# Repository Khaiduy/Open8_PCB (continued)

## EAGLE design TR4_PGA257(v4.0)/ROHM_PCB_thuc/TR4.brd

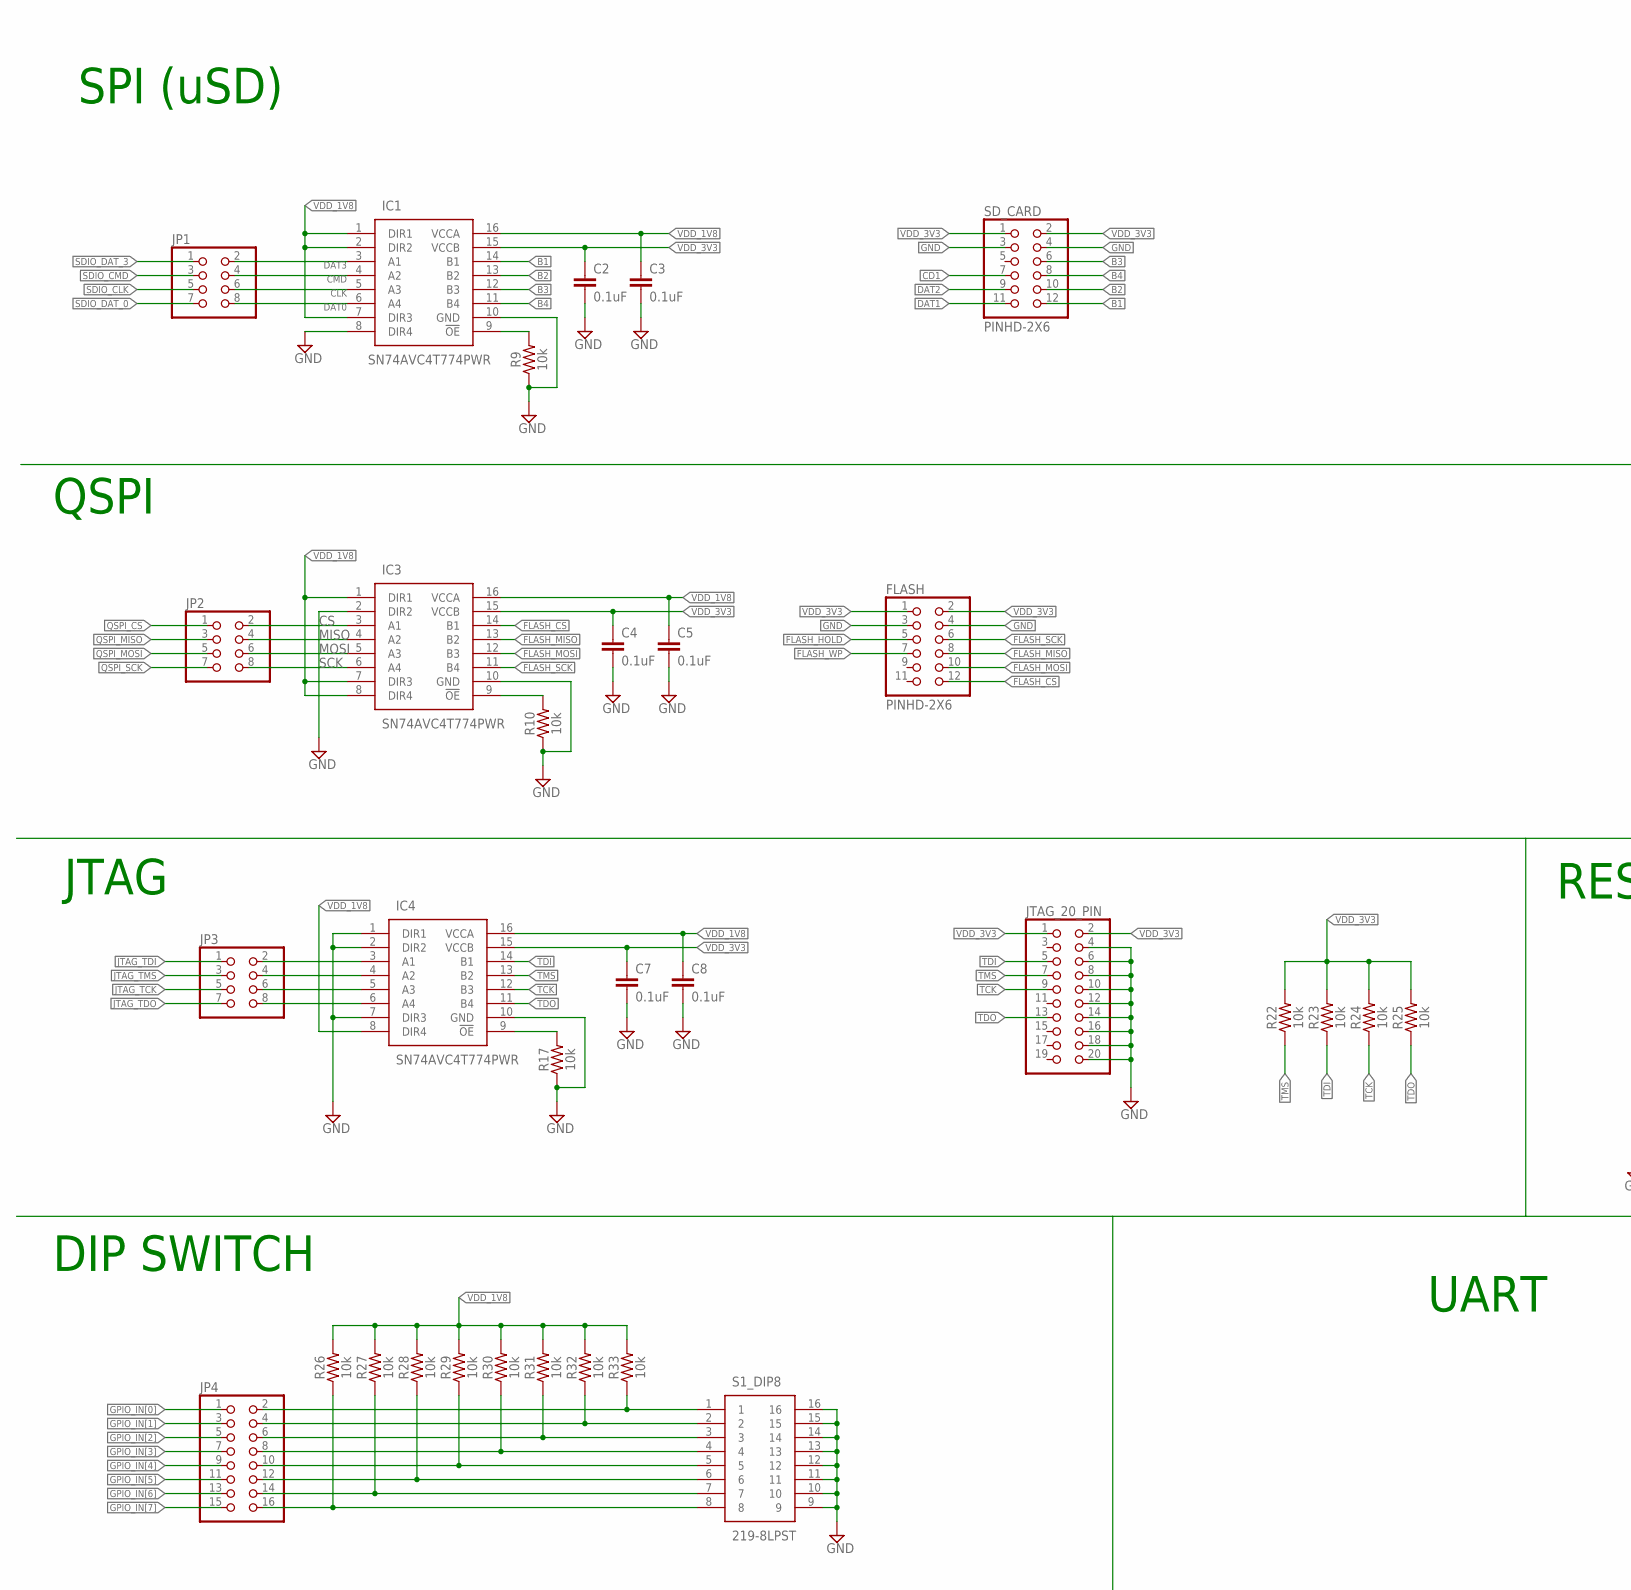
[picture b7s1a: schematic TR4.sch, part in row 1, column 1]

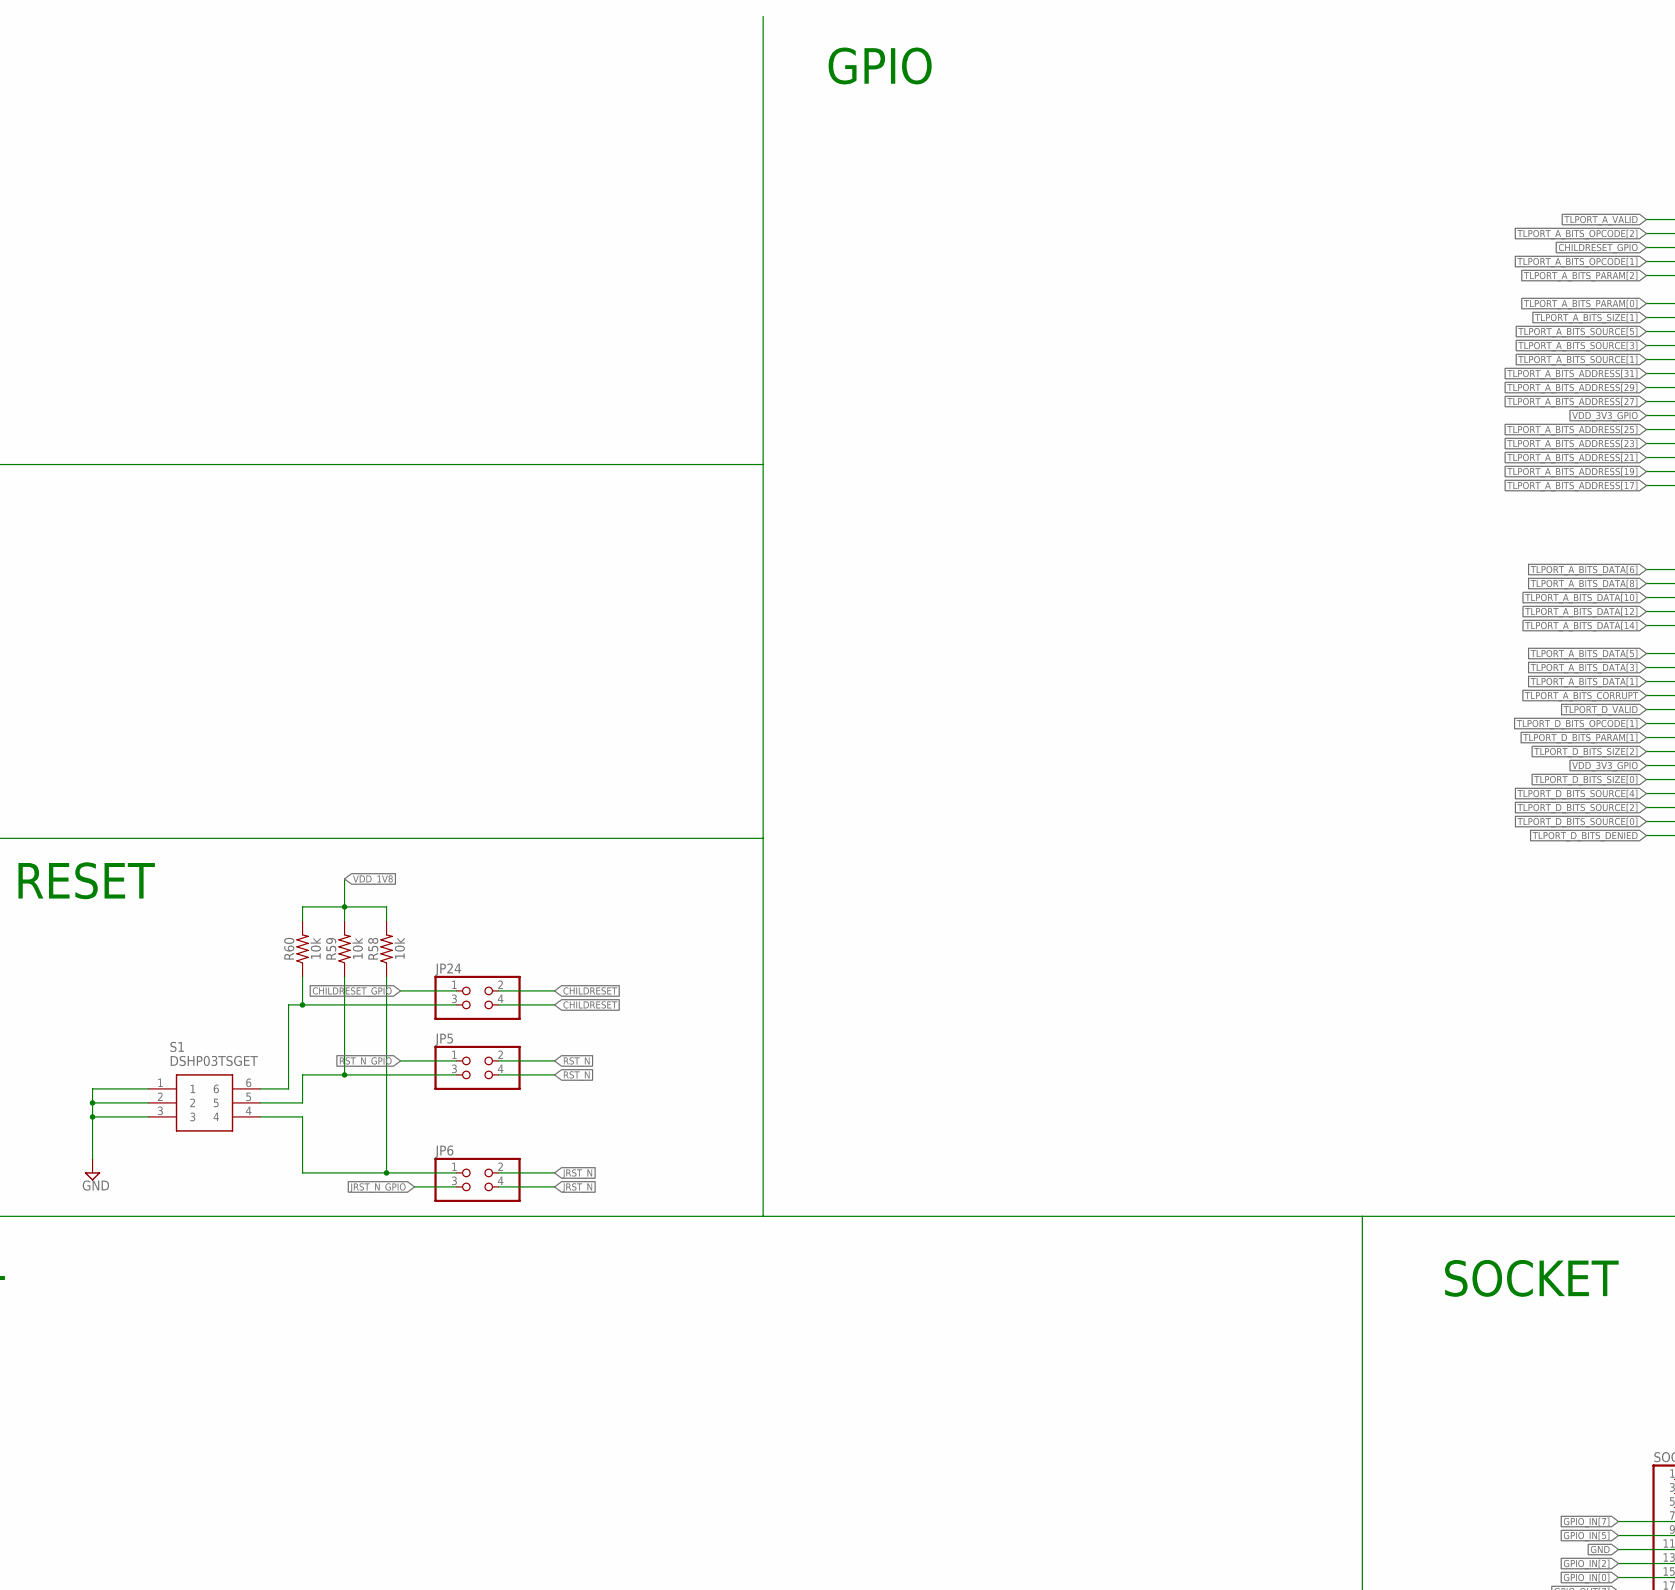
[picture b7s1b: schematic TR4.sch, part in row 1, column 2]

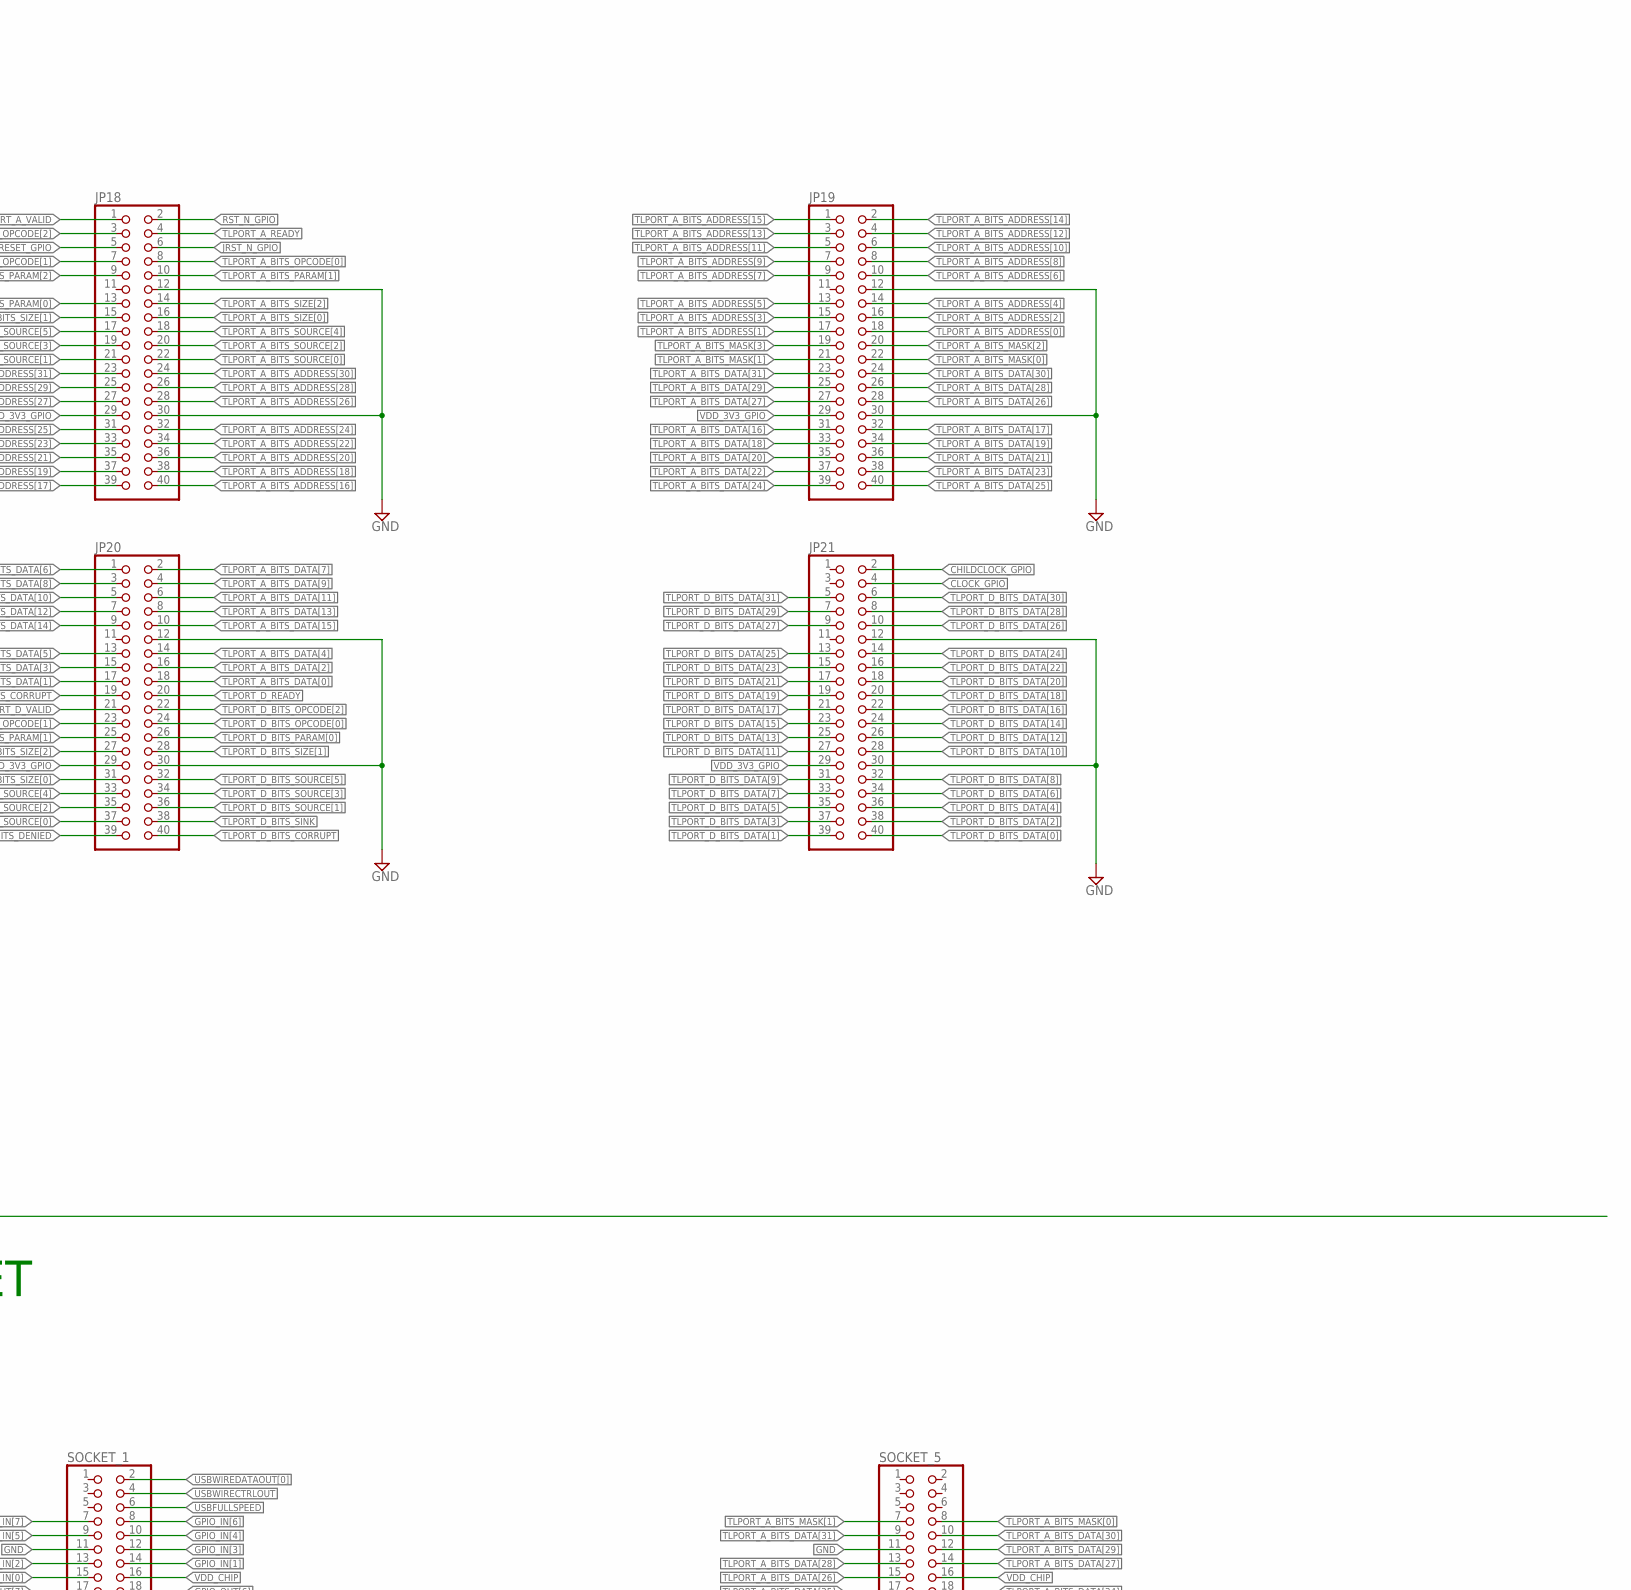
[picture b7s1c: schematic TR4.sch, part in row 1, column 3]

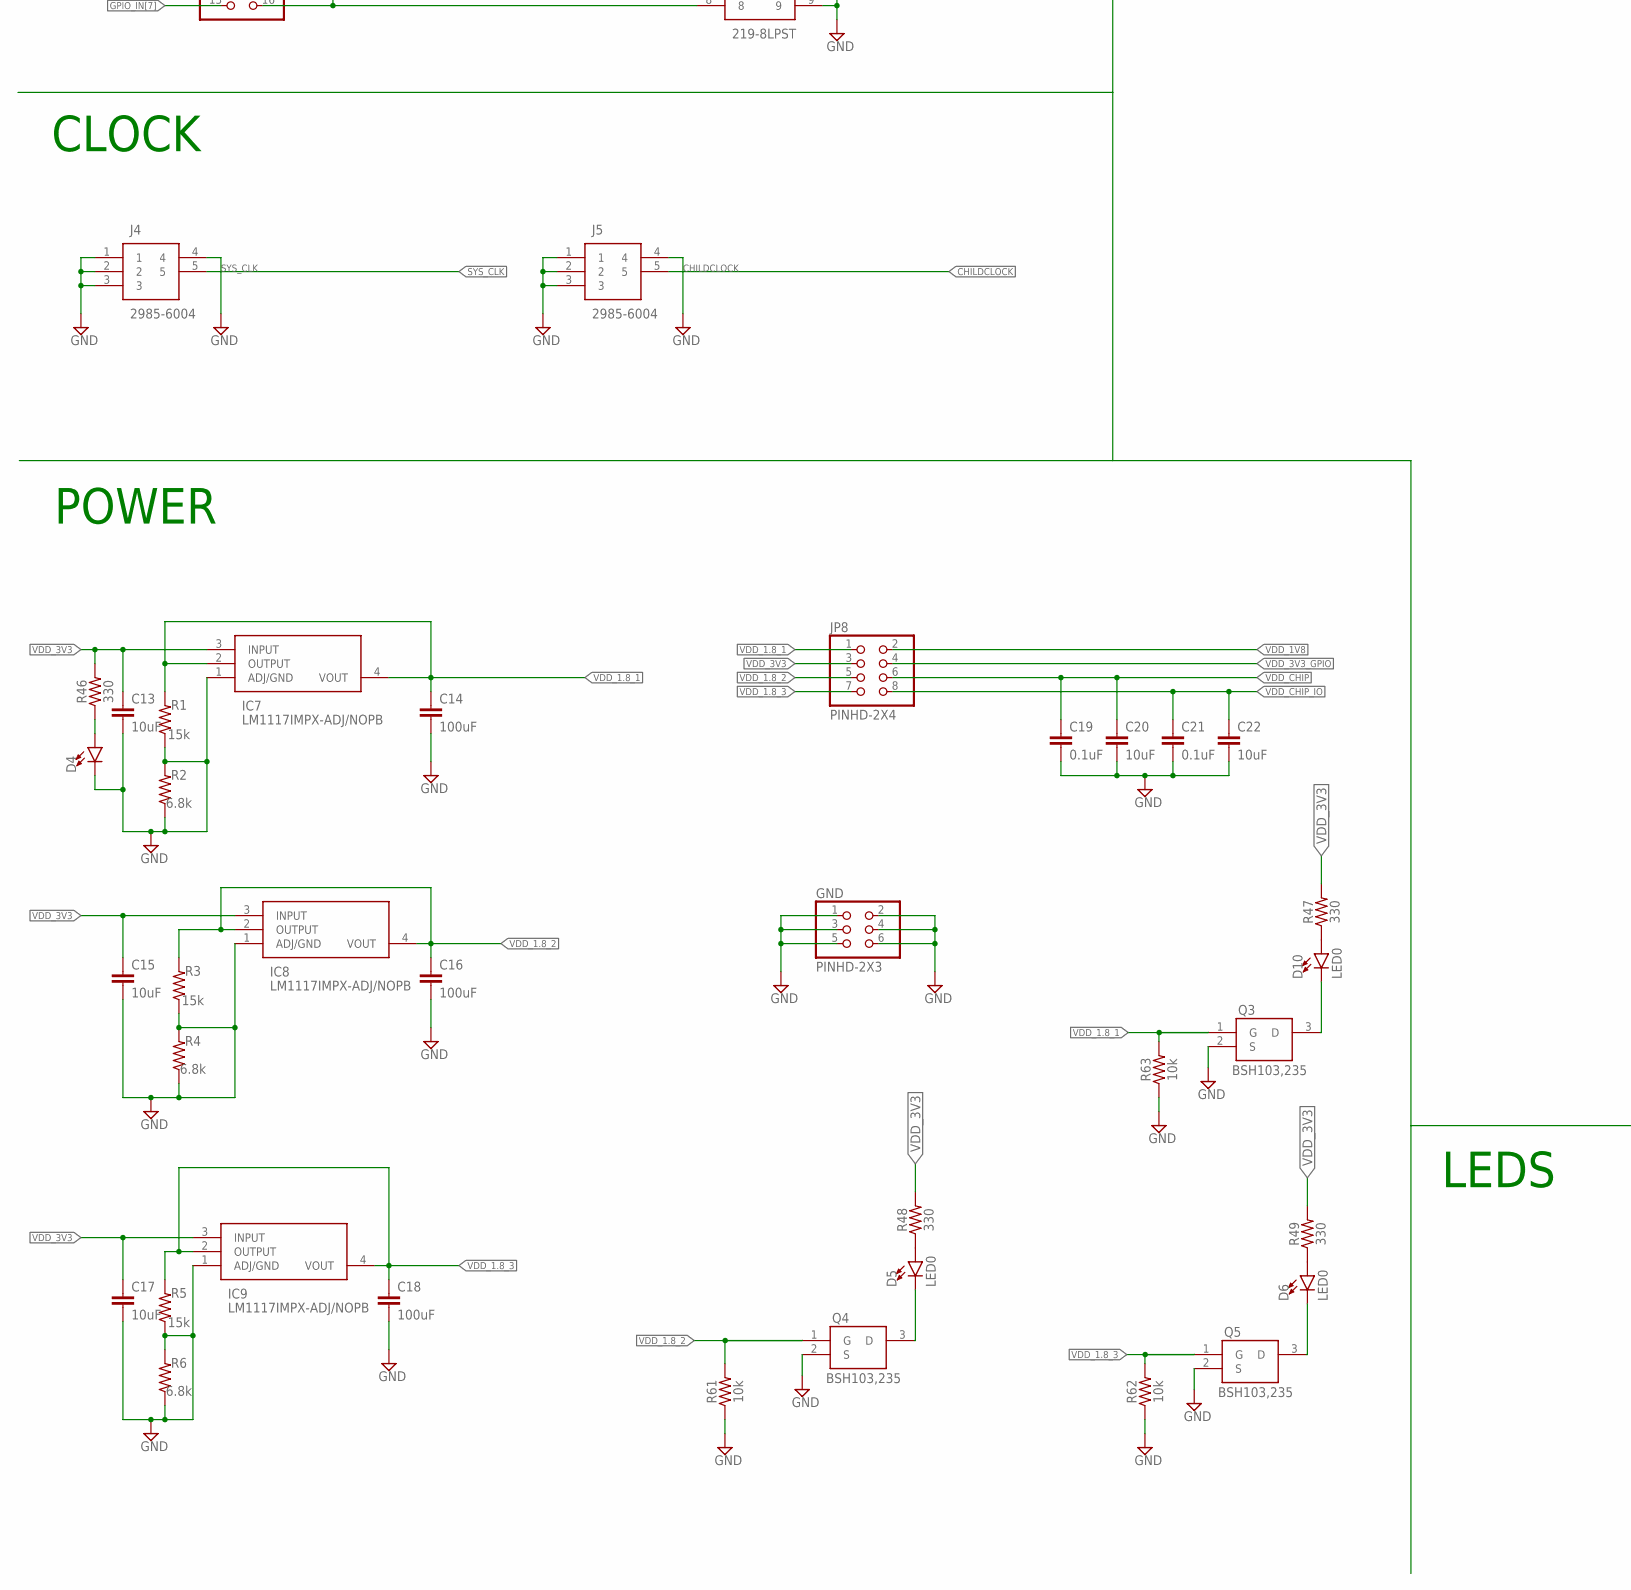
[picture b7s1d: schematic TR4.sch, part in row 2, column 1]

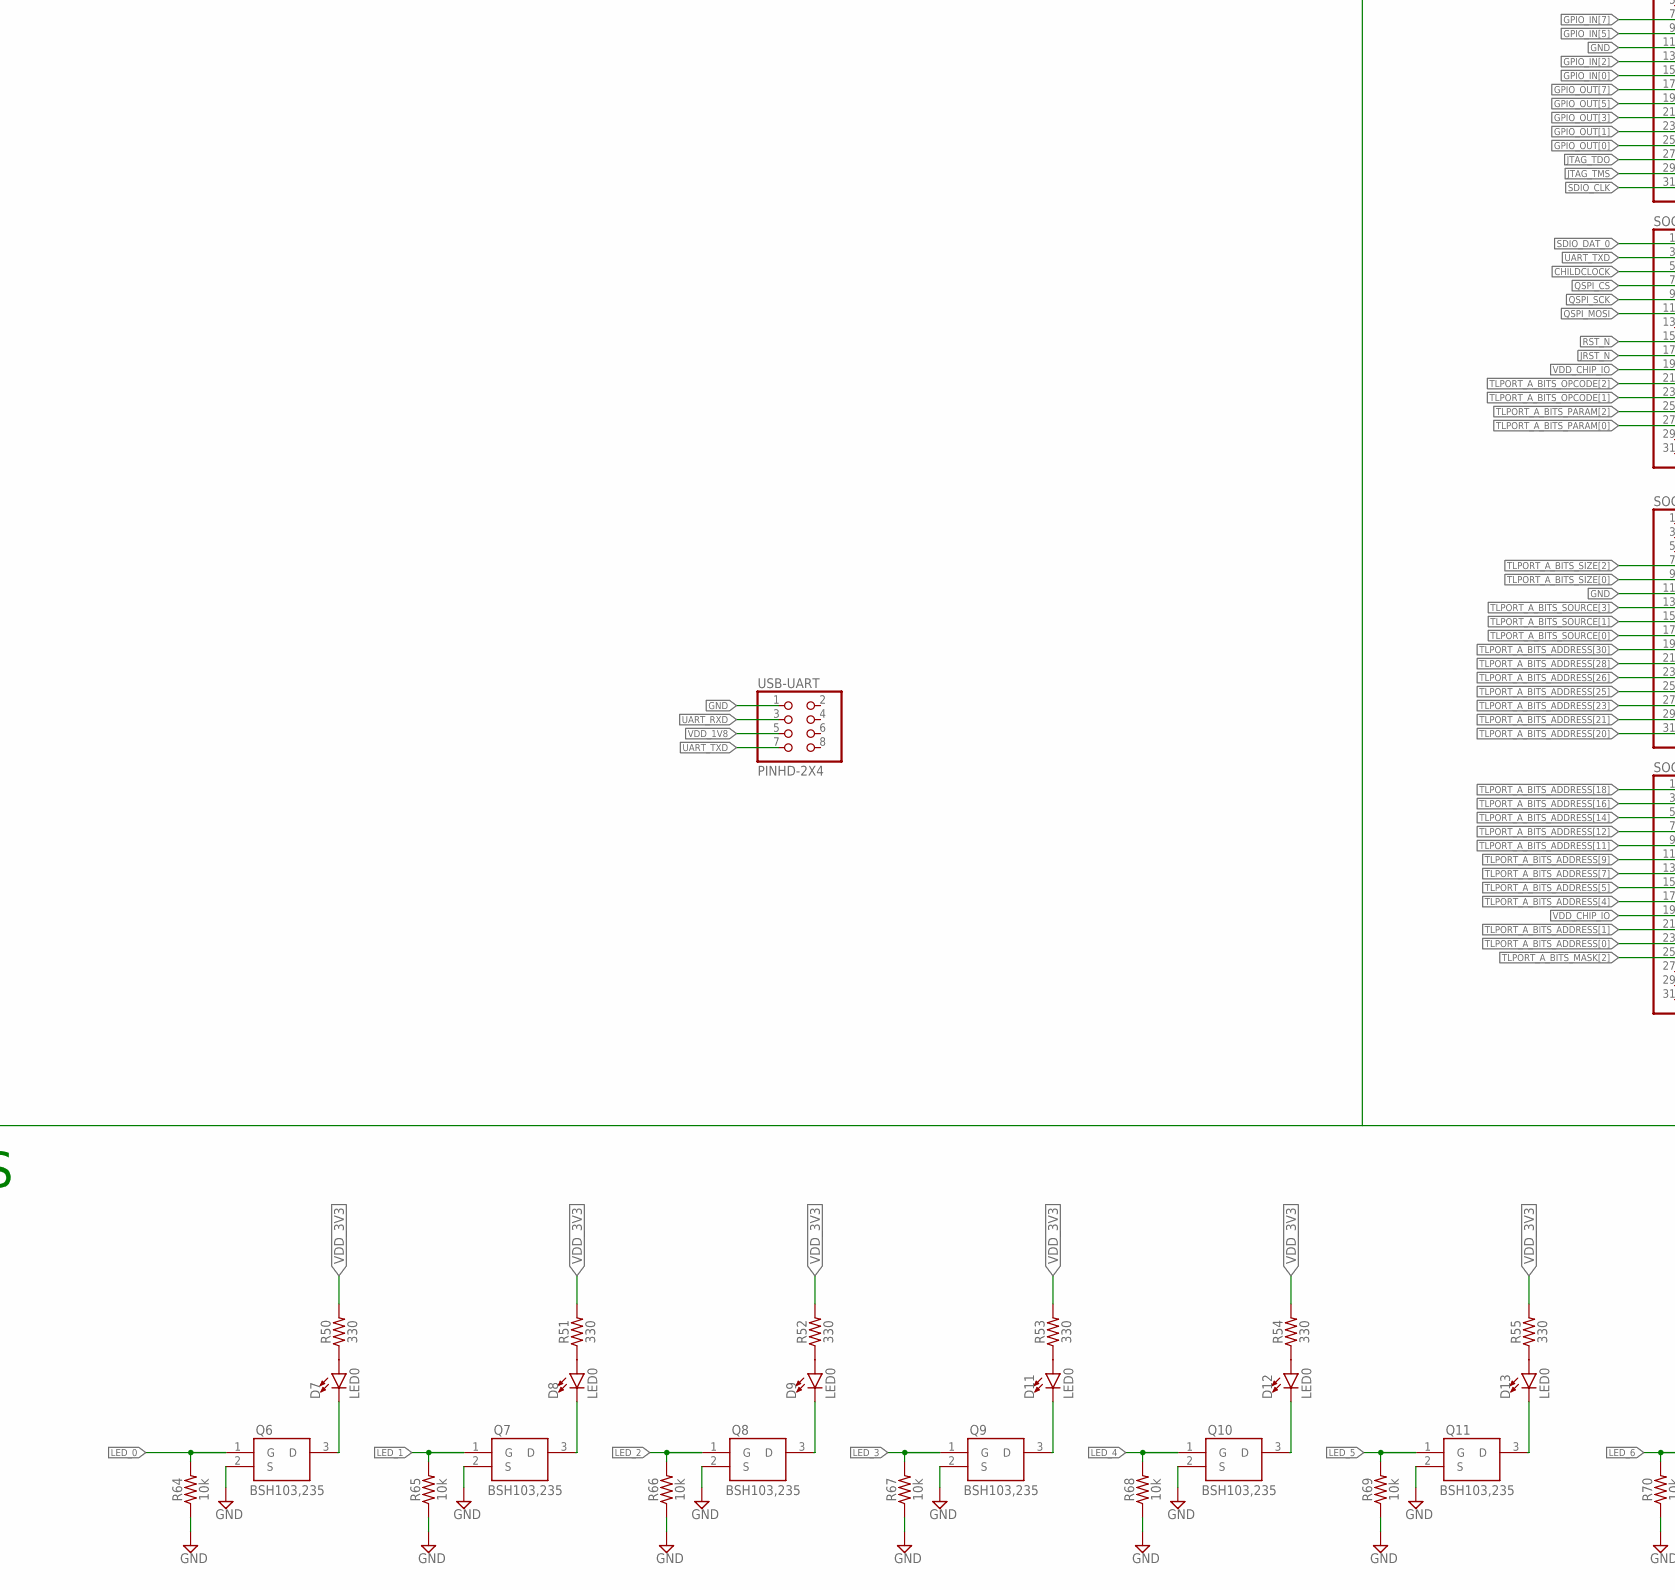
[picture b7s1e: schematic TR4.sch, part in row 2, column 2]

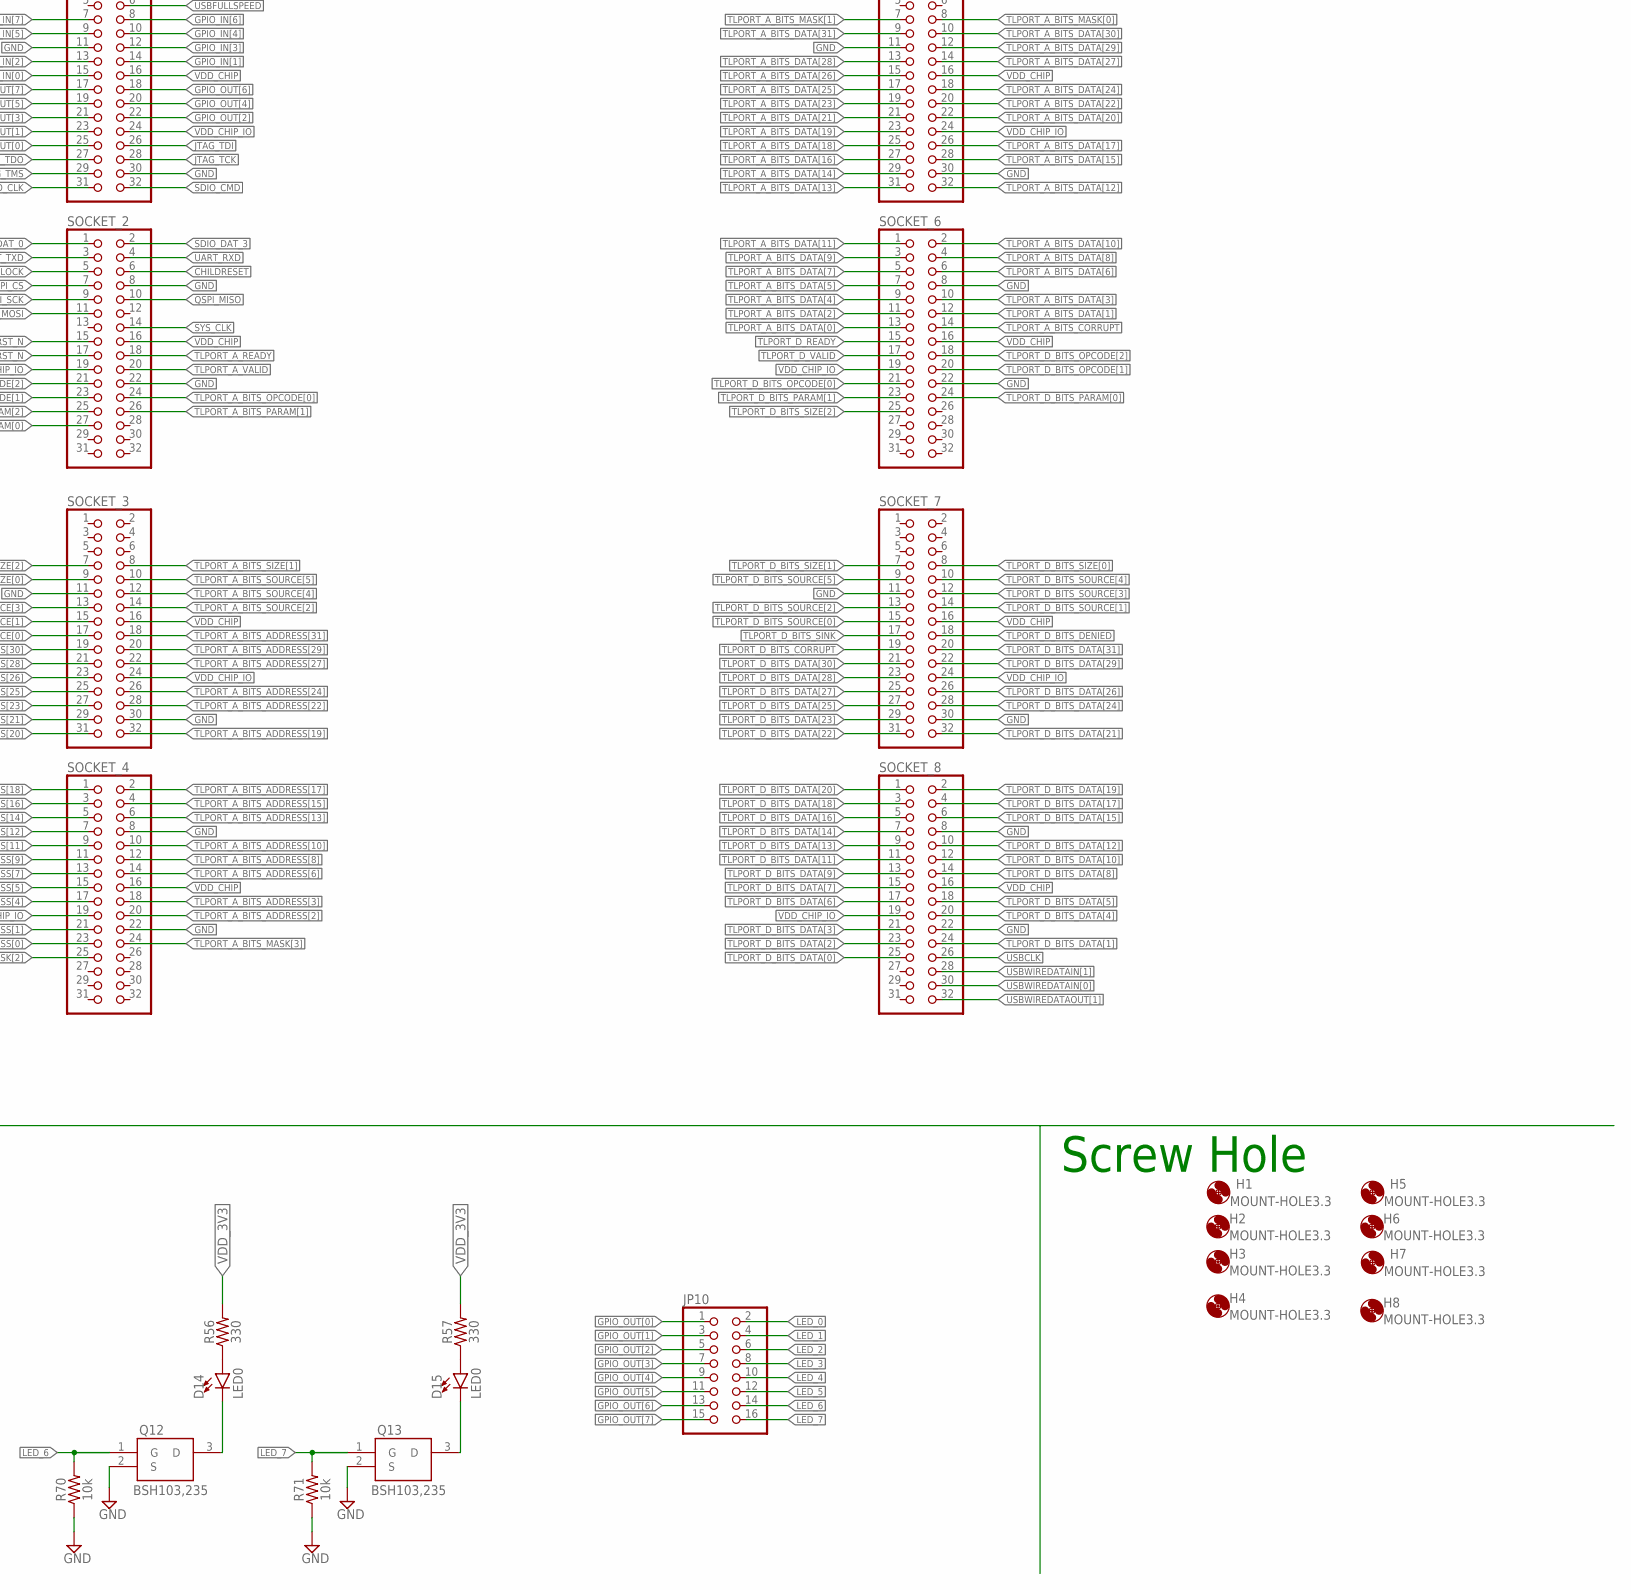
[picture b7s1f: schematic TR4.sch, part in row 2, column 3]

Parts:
C2, C3, C4, C5, C7, C8, C19, C21: 0.1uF; 0603
C13, C15, C17, C20, C22: 10uF; 0603
C14, C16, C18: 100uF; 0603
D4: LED0603; LED-0603
D5, D6, D7, D8, D9, D10, D11, D12, D13, D14, D15: LED0; LED-0603
FLASH: PINHD-2X6; 2X06
GND: PINHD-2X3; 2X03
H1, H2, H3, H4, H5, H6, H7, H8: MOUNT-HOLE3.3; 3,3
IC1, IC3, IC4: SN74AVC4T774PWR; SOP65P640X120-16N
IC7, IC8, IC9: LM1117IMPX-ADJ/NOPB; SOT230P700X180-4N
J4, J5: 2985-6004; 29856004
JP1, JP2, JP3, JP8: PINHD-2X4; 2X04
JP4, JP10: PINHD-2X8; 2X08
JP5, JP6, JP24: PINHD-2X2; 2X02
JP18, JP19, JP20, JP21: PINHD-2X20; 2X20
JTAG_20_PIN: PINHD-2X10; 2X10
Q3, Q4, Q5, Q6, Q7, Q8, Q9, Q10, Q11, Q12, Q13: BSH103,235; SOT95P230X110-3N
R1, R3, R5: 15k; 0603
R2, R4, R6: 6.8k; 0603
R9, R10, R17, R22, R23, R24, R25, R26, R27, R28, R29, R30, R31, R32, R33, R58, R59, R60, R61, R62, R63, R64, R65, R66, R67, R68, R69, R70, R71: 10k; 0603
R46, R47, R48, R49, R50, R51, R52, R53, R54, R55, R56, R57: 330; 0603
S1: DSHP03TSGET; SOT127P835X260-6N
S1_DIP8: 219-8LPST; 2198LPST
SD_CARD: PINHD-2X6; 2X06
SOCKET_1, SOCKET_2, SOCKET_3, SOCKET_4, SOCKET_5, SOCKET_6, SOCKET_7, SOCKET_8: PINHD-2X16; 2X16
USB-UART: PINHD-2X4; 2X04

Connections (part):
B1: IC1.14 (B1), SD_CARD.12
B2: IC1.13 (B2), SD_CARD.10
B3: IC1.12 (B3), SD_CARD.6
B4: IC1.11 (B4), SD_CARD.8
CD1: SD_CARD.7
CHILDCLOCK: J5.5, SOCKET_2.5
CHILDCLOCK_GPIO: JP21.2
CHILDRESET: JP24.2, JP24.4, SOCKET_2.6
CHILDRESET_GPIO: JP18.5, JP24.1
CLK: IC1.5 (A3), JP1.6
CLOCK_GPIO: JP21.4
CMD: IC1.4 (A2), JP1.4
CS: IC3.3 (A1), JP2.2
DAT0: IC1.6 (A4), JP1.8
DAT1: SD_CARD.11
DAT2: SD_CARD.9
DAT3: IC1.3 (A1), JP1.2
FLASH_CS: FLASH.12, IC3.14 (B1)
FLASH_HOLD: FLASH.5
FLASH_MISO: FLASH.8, IC3.13 (B2)
FLASH_MOSI: FLASH.10, IC3.12 (B3)
FLASH_SCK: FLASH.6, IC3.11 (B4)
FLASH_WP: FLASH.7
GND: C2.2, C3.2, C4.2, C5.2, C7.2, C8.2, C13.2, C14.2, C15.2, C16.2, C17.2, C18.2, C19.2, C20.2, C21.2, C22.2, D4.C, FLASH.3, FLASH.4, GND.1, GND.2, GND.3, GND.4, GND.5, GND.6, IC1.8 (DIR4), IC1.10 (GND), IC3.2 (DIR2), IC3.10 (GND), IC4.1 (DIR1), IC4.2 (DIR2), IC4.7 (DIR3), IC4.10 (GND), IC7.1 (ADJ/GND), IC8.1 (ADJ/GND), IC9.1 (ADJ/GND), J4.1, J4.2, J4.3, J4.4, J5.1, J5.2, J5.3, J5.4, JP18.12, JP18.30, JP19.12, JP19.30, JP20.12, JP20.30, JP21.12, JP21.30, JTAG_20_PIN.4, JTAG_20_PIN.6, JTAG_20_PIN.8, JTAG_20_PIN.10, JTAG_20_PIN.12, JTAG_20_PIN.14, JTAG_20_PIN.16, JTAG_20_PIN.18, JTAG_20_PIN.20, Q3.2 (S), Q4.2 (S), Q5.2 (S), Q6.2 (S), Q7.2 (S), Q8.2 (S), Q9.2 (S), Q10.2 (S), Q11.2 (S), Q12.2 (S), Q13.2 (S), R1.1, R2.1, R2.2, R3.1, R4.1, R4.2, R5.1, R6.1, R6.2, R9.1, R10.1, R17.1, R61.1, R62.1, R63.1, R64.1, R65.1, R66.1, R67.1, R68.1, R69.1, R70.1, R71.1, S1.1, S1.2, S1.3, S1_DIP8.9, S1_DIP8.10, S1_DIP8.11, S1_DIP8.12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
GPIO_IN[0]: JP4.1, SOCKET_1.15
GPIO_IN[1]: JP4.3, SOCKET_1.14
GPIO_IN[2]: JP4.5, SOCKET_1.13
GPIO_IN[3]: JP4.7, SOCKET_1.12
GPIO_IN[4]: JP4.9, SOCKET_1.10
GPIO_IN[5]: JP4.11, SOCKET_1.9
GPIO_IN[6]: JP4.13, SOCKET_1.8
GPIO_IN[7]: JP4.15, SOCKET_1.7
GPIO_OUT[0]: JP10.1, SOCKET_1.25
GPIO_OUT[1]: JP10.3, SOCKET_1.23
GPIO_OUT[2]: JP10.5, SOCKET_1.22
GPIO_OUT[3]: JP10.7, SOCKET_1.21
GPIO_OUT[4]: JP10.9, SOCKET_1.20
GPIO_OUT[5]: JP10.11, SOCKET_1.19
GPIO_OUT[6]: JP10.13, SOCKET_1.18
GPIO_OUT[7]: JP10.15, SOCKET_1.17
JRST_N: JP6.2, JP6.4, SOCKET_2.17
JRST_N_GPIO: JP6.3, JP18.6
JTAG_TCK: JP3.5, SOCKET_1.28
JTAG_TDI: JP3.1, SOCKET_1.26
JTAG_TDO: JP3.7, SOCKET_1.27
JTAG_TMS: JP3.3, SOCKET_1.29
LED_0: JP10.2, Q6.1 (G), R64.2
LED_1: JP10.4, Q7.1 (G), R65.2
LED_2: JP10.6, Q8.1 (G), R66.2
LED_3: JP10.8, Q9.1 (G), R67.2
LED_4: JP10.10, Q10.1 (G), R68.2
LED_5: JP10.12, Q11.1 (G), R69.2
LED_6: JP10.14, Q12.1 (G), R70.2
LED_7: JP10.16, Q13.1 (G), R71.2
MISO: IC3.4 (A2), JP2.4
MOSI: IC3.5 (A3), JP2.6
unnamed: IC1.9 (!OE), R9.2
unnamed: IC3.9 (!OE), R10.2
unnamed: IC4.3 (A1), JP3.2
unnamed: IC4.4 (A2), JP3.4
unnamed: IC4.5 (A3), JP3.6
unnamed: IC4.6 (A4), JP3.8
unnamed: IC4.9 (!OE), R17.2
unnamed: JP4.2, R33.1, S1_DIP8.1
unnamed: JP4.4, R32.1, S1_DIP8.2
unnamed: JP4.6, R31.1, S1_DIP8.3
unnamed: JP4.8, R30.1, S1_DIP8.4
unnamed: JP4.10, R29.1, S1_DIP8.5
unnamed: JP4.12, R28.1, S1_DIP8.6
unnamed: JP4.14, R27.1, S1_DIP8.7
unnamed: JP4.16, R26.1, S1_DIP8.8
unnamed: JP5.3, R59.1, S1.5
unnamed: JP24.3, R60.1, S1.6
unnamed: D4.A, R46.1
unnamed: D10.A, R47.1
unnamed: D10.C, Q3.3 (D)
unnamed: JP6.1, R58.1, S1.4
unnamed: D5.A, R48.1
unnamed: D5.C, Q4.3 (D)
unnamed: D6.A, R49.1
unnamed: D6.C, Q5.3 (D)
unnamed: D7.A, R50.1
unnamed: D7.C, Q6.3 (D)
unnamed: D8.A, R51.1
unnamed: D8.C, Q7.3 (D)
unnamed: D9.A, R52.1
unnamed: D9.C, Q8.3 (D)
unnamed: D11.A, R53.1
unnamed: D11.C, Q9.3 (D)
unnamed: D12.A, R54.1
unnamed: D12.C, Q10.3 (D)
unnamed: D13.A, R55.1
unnamed: D13.C, Q11.3 (D)
unnamed: D14.A, R56.1
unnamed: D14.C, Q12.3 (D)
unnamed: D15.A, R57.1
unnamed: D15.C, Q13.3 (D)
QSPI_CS: JP2.1, SOCKET_2.7
QSPI_MISO: JP2.3, SOCKET_2.10
QSPI_MOSI: JP2.5, SOCKET_2.11
QSPI_SCK: JP2.7, SOCKET_2.9
RST_N: JP5.2, JP5.4, SOCKET_2.15
RST_N_GPIO: JP5.1, JP18.2
SCK: IC3.6 (A4), JP2.8
SDIO_CLK: JP1.5, SOCKET_1.31
SDIO_CMD: JP1.3, SOCKET_1.32
SDIO_DAT_0: JP1.7, SOCKET_2.1
SDIO_DAT_3: JP1.1, SOCKET_2.2
SYS_CLK: J4.5, SOCKET_2.14
TCK: IC4.12 (B3), JTAG_20_PIN.9, R24.1
TDI: IC4.14 (B1), JTAG_20_PIN.5, R23.1
TDO: IC4.11 (B4), JTAG_20_PIN.13, R25.1
TLPORT_A_BITS_ADDRESS[0]: JP19.18, SOCKET_4.23
TLPORT_A_BITS_ADDRESS[1]: JP19.17, SOCKET_4.21
TLPORT_A_BITS_ADDRESS[2]: JP19.16, SOCKET_4.20
TLPORT_A_BITS_ADDRESS[3]: JP19.15, SOCKET_4.18
TLPORT_A_BITS_ADDRESS[4]: JP19.14, SOCKET_4.17
TLPORT_A_BITS_ADDRESS[5]: JP19.13, SOCKET_4.15
TLPORT_A_BITS_ADDRESS[6]: JP19.10, SOCKET_4.14
TLPORT_A_BITS_ADDRESS[7]: JP19.9, SOCKET_4.13
TLPORT_A_BITS_ADDRESS[8]: JP19.8, SOCKET_4.12
TLPORT_A_BITS_ADDRESS[9]: JP19.7, SOCKET_4.11
TLPORT_A_BITS_ADDRESS[10]: JP19.6, SOCKET_4.10
TLPORT_A_BITS_ADDRESS[11]: JP19.5, SOCKET_4.9
TLPORT_A_BITS_ADDRESS[12]: JP19.4, SOCKET_4.7
TLPORT_A_BITS_ADDRESS[13]: JP19.3, SOCKET_4.6
TLPORT_A_BITS_ADDRESS[14]: JP19.2, SOCKET_4.5
TLPORT_A_BITS_ADDRESS[15]: JP19.1, SOCKET_4.4
TLPORT_A_BITS_ADDRESS[16]: JP18.40, SOCKET_4.3
TLPORT_A_BITS_ADDRESS[17]: JP18.39, SOCKET_4.2
TLPORT_A_BITS_ADDRESS[18]: JP18.38, SOCKET_4.1
TLPORT_A_BITS_ADDRESS[19]: JP18.37, SOCKET_3.32
TLPORT_A_BITS_ADDRESS[20]: JP18.36, SOCKET_3.31
TLPORT_A_BITS_ADDRESS[21]: JP18.35, SOCKET_3.29
TLPORT_A_BITS_ADDRESS[22]: JP18.34, SOCKET_3.28
TLPORT_A_BITS_ADDRESS[23]: JP18.33, SOCKET_3.27
TLPORT_A_BITS_ADDRESS[24]: JP18.32, SOCKET_3.26
TLPORT_A_BITS_ADDRESS[25]: JP18.31, SOCKET_3.25
TLPORT_A_BITS_ADDRESS[26]: JP18.28, SOCKET_3.23
TLPORT_A_BITS_ADDRESS[27]: JP18.27, SOCKET_3.22
TLPORT_A_BITS_ADDRESS[28]: JP18.26, SOCKET_3.21
TLPORT_A_BITS_ADDRESS[29]: JP18.25, SOCKET_3.20
TLPORT_A_BITS_ADDRESS[30]: JP18.24, SOCKET_3.19
TLPORT_A_BITS_ADDRESS[31]: JP18.23, SOCKET_3.18
TLPORT_A_BITS_CORRUPT: JP20.19, SOCKET_6.14
TLPORT_A_BITS_DATA[0]: JP20.18, SOCKET_6.13
TLPORT_A_BITS_DATA[1]: JP20.17, SOCKET_6.12
TLPORT_A_BITS_DATA[2]: JP20.16, SOCKET_6.11
TLPORT_A_BITS_DATA[3]: JP20.15, SOCKET_6.10
TLPORT_A_BITS_DATA[4]: JP20.14, SOCKET_6.9
TLPORT_A_BITS_DATA[5]: JP20.13, SOCKET_6.7
TLPORT_A_BITS_DATA[6]: JP20.1, SOCKET_6.6
TLPORT_A_BITS_DATA[7]: JP20.2, SOCKET_6.5
TLPORT_A_BITS_DATA[8]: JP20.3, SOCKET_6.4
TLPORT_A_BITS_DATA[9]: JP20.4, SOCKET_6.3
TLPORT_A_BITS_DATA[10]: JP20.5, SOCKET_6.2
TLPORT_A_BITS_DATA[11]: JP20.6, SOCKET_6.1
TLPORT_A_BITS_DATA[12]: JP20.7, SOCKET_5.32
TLPORT_A_BITS_DATA[13]: JP20.8, SOCKET_5.31
TLPORT_A_BITS_DATA[14]: JP20.9, SOCKET_5.29
TLPORT_A_BITS_DATA[15]: JP20.10, SOCKET_5.28
TLPORT_A_BITS_DATA[16]: JP19.31, SOCKET_5.27
TLPORT_A_BITS_DATA[17]: JP19.32, SOCKET_5.26
TLPORT_A_BITS_DATA[18]: JP19.33, SOCKET_5.25
TLPORT_A_BITS_DATA[19]: JP19.34, SOCKET_5.23
TLPORT_A_BITS_DATA[20]: JP19.35, SOCKET_5.22
TLPORT_A_BITS_DATA[21]: JP19.36, SOCKET_5.21
TLPORT_A_BITS_DATA[22]: JP19.37, SOCKET_5.20
TLPORT_A_BITS_DATA[23]: JP19.38, SOCKET_5.19
TLPORT_A_BITS_DATA[24]: JP19.39, SOCKET_5.18
TLPORT_A_BITS_DATA[25]: JP19.40, SOCKET_5.17
TLPORT_A_BITS_DATA[26]: JP19.28, SOCKET_5.15
TLPORT_A_BITS_DATA[27]: JP19.27, SOCKET_5.14
TLPORT_A_BITS_DATA[28]: JP19.26, SOCKET_5.13
TLPORT_A_BITS_DATA[29]: JP19.25, SOCKET_5.12
TLPORT_A_BITS_DATA[30]: JP19.24, SOCKET_5.10
TLPORT_A_BITS_DATA[31]: JP19.23, SOCKET_5.9
TLPORT_A_BITS_MASK[0]: JP19.22, SOCKET_5.8
TLPORT_A_BITS_MASK[1]: JP19.21, SOCKET_5.7
TLPORT_A_BITS_MASK[2]: JP19.20, SOCKET_4.25
TLPORT_A_BITS_MASK[3]: JP19.19, SOCKET_4.24
TLPORT_A_BITS_OPCODE[0]: JP18.8, SOCKET_2.24
TLPORT_A_BITS_OPCODE[1]: JP18.7, SOCKET_2.23
TLPORT_A_BITS_OPCODE[2]: JP18.3, SOCKET_2.21
TLPORT_A_BITS_PARAM[0]: JP18.13, SOCKET_2.27
TLPORT_A_BITS_PARAM[1]: JP18.10, SOCKET_2.26
TLPORT_A_BITS_PARAM[2]: JP18.9, SOCKET_2.25
TLPORT_A_BITS_SIZE[0]: JP18.16, SOCKET_3.9
TLPORT_A_BITS_SIZE[1]: JP18.15, SOCKET_3.8
TLPORT_A_BITS_SIZE[2]: JP18.14, SOCKET_3.7
TLPORT_A_BITS_SOURCE[0]: JP18.22, SOCKET_3.17
TLPORT_A_BITS_SOURCE[1]: JP18.21, SOCKET_3.15
TLPORT_A_BITS_SOURCE[2]: JP18.20, SOCKET_3.14
TLPORT_A_BITS_SOURCE[3]: JP18.19, SOCKET_3.13
TLPORT_A_BITS_SOURCE[4]: JP18.18, SOCKET_3.12
TLPORT_A_BITS_SOURCE[5]: JP18.17, SOCKET_3.10
TLPORT_A_READY: JP18.4, SOCKET_2.18
TLPORT_A_VALID: JP18.1, SOCKET_2.20
TLPORT_D_BITS_CORRUPT: JP20.40, SOCKET_7.19
TLPORT_D_BITS_DATA[0]: JP21.40, SOCKET_8.25
TLPORT_D_BITS_DATA[1]: JP21.39, SOCKET_8.24
TLPORT_D_BITS_DATA[2]: JP21.38, SOCKET_8.23
TLPORT_D_BITS_DATA[3]: JP21.37, SOCKET_8.21
TLPORT_D_BITS_DATA[4]: JP21.36, SOCKET_8.20
TLPORT_D_BITS_DATA[5]: JP21.35, SOCKET_8.18
TLPORT_D_BITS_DATA[6]: JP21.34, SOCKET_8.17
TLPORT_D_BITS_DATA[7]: JP21.33, SOCKET_8.15
TLPORT_D_BITS_DATA[8]: JP21.32, SOCKET_8.14
TLPORT_D_BITS_DATA[9]: JP21.31, SOCKET_8.13
TLPORT_D_BITS_DATA[10]: JP21.28, SOCKET_8.12
TLPORT_D_BITS_DATA[11]: JP21.27, SOCKET_8.11
TLPORT_D_BITS_DATA[12]: JP21.26, SOCKET_8.10
TLPORT_D_BITS_DATA[13]: JP21.25, SOCKET_8.9
TLPORT_D_BITS_DATA[14]: JP21.24, SOCKET_8.7
TLPORT_D_BITS_DATA[15]: JP21.23, SOCKET_8.6
TLPORT_D_BITS_DATA[16]: JP21.22, SOCKET_8.5
TLPORT_D_BITS_DATA[17]: JP21.21, SOCKET_8.4
TLPORT_D_BITS_DATA[18]: JP21.20, SOCKET_8.3
TLPORT_D_BITS_DATA[19]: JP21.19, SOCKET_8.2
TLPORT_D_BITS_DATA[20]: JP21.18, SOCKET_8.1
TLPORT_D_BITS_DATA[21]: JP21.17, SOCKET_7.32
TLPORT_D_BITS_DATA[22]: JP21.16, SOCKET_7.31
TLPORT_D_BITS_DATA[23]: JP21.15, SOCKET_7.29
TLPORT_D_BITS_DATA[24]: JP21.14, SOCKET_7.28
TLPORT_D_BITS_DATA[25]: JP21.13, SOCKET_7.27
TLPORT_D_BITS_DATA[26]: JP21.10, SOCKET_7.26
TLPORT_D_BITS_DATA[27]: JP21.9, SOCKET_7.25
TLPORT_D_BITS_DATA[28]: JP21.8, SOCKET_7.23
TLPORT_D_BITS_DATA[29]: JP21.7, SOCKET_7.22
TLPORT_D_BITS_DATA[30]: JP21.6, SOCKET_7.21
TLPORT_D_BITS_DATA[31]: JP21.5, SOCKET_7.20
TLPORT_D_BITS_DENIED: JP20.39, SOCKET_7.18
TLPORT_D_BITS_OPCODE[0]: JP20.24, SOCKET_6.21
TLPORT_D_BITS_OPCODE[1]: JP20.23, SOCKET_6.20
TLPORT_D_BITS_OPCODE[2]: JP20.22, SOCKET_6.18
TLPORT_D_BITS_PARAM[0]: JP20.26, SOCKET_6.24
TLPORT_D_BITS_PARAM[1]: JP20.25, SOCKET_6.23
TLPORT_D_BITS_SINK: JP20.38, SOCKET_7.17
TLPORT_D_BITS_SIZE[0]: JP20.31, SOCKET_7.8
TLPORT_D_BITS_SIZE[1]: JP20.28, SOCKET_7.7
TLPORT_D_BITS_SIZE[2]: JP20.27, SOCKET_6.25
TLPORT_D_BITS_SOURCE[0]: JP20.37, SOCKET_7.15
TLPORT_D_BITS_SOURCE[1]: JP20.36, SOCKET_7.14
TLPORT_D_BITS_SOURCE[2]: JP20.35, SOCKET_7.13
TLPORT_D_BITS_SOURCE[3]: JP20.34, SOCKET_7.12
TLPORT_D_BITS_SOURCE[4]: JP20.33, SOCKET_7.10
TLPORT_D_BITS_SOURCE[5]: JP20.32, SOCKET_7.9
TLPORT_D_READY: JP20.20, SOCKET_6.15
TLPORT_D_VALID: JP20.21, SOCKET_6.17
TMS: IC4.13 (B2), JTAG_20_PIN.7, R22.1
UART_RXD: SOCKET_2.4, USB-UART.3
UART_TXD: SOCKET_2.3, USB-UART.7
USBCLK: SOCKET_8.26
USBFULLSPEED: SOCKET_1.6
USBWIRECTRLOUT: SOCKET_1.4
USBWIREDATAIN[0]: SOCKET_8.30
USBWIREDATAIN[1]: SOCKET_8.28
USBWIREDATAOUT[0]: SOCKET_1.2
USBWIREDATAOUT[1]: SOCKET_8.32
VDD_1.8_1: C14.1, IC7.2 (OUTPUT), IC7.4 (VOUT), JP8.1, Q3.1 (G), R1.2, R63.2
VDD_1.8_2: C16.1, IC8.2 (OUTPUT), IC8.4 (VOUT), JP8.5, Q4.1 (G), R3.2, R61.2
VDD_1.8_3: C18.1, IC9.2 (OUTPUT), IC9.4 (VOUT), JP8.7, Q5.1 (G), R5.2, R62.2
VDD_1V8: C3.1, C5.1, C8.1, IC1.1 (DIR1), IC1.2 (DIR2), IC1.7 (DIR3), IC1.16 (VCCA), IC3.1 (DIR1), IC3.7 (DIR3), IC3.8 (DIR4), IC3.16 (VCCA), IC4.8 (DIR4), IC4.16 (VCCA), JP8.2, R26.2, R27.2, R28.2, R29.2, R30.2, R31.2, R32.2, R33.2, R58.2, R59.2, R60.2, USB-UART.5
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
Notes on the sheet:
QSPI
SPI (uSD)
JTAG
DIP SWITCH
CLOCK
UART
POWER
LEDS
SOCKET
GPIO
Screw Hole
RESET
